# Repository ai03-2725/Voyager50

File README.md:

# Voyager50
A balance between function and size

[Supported layouts](http://www.keyboard-layout-editor.com/#/gists/caf09ce52668a0b0574eaae53debacd4)  

#### In light of recent claims that I am 100% liable for any of my open source PCBs, I am adding this disclaimer.
#### I provide these PCBs as a reference for designing keyboard PCBs. Using them within your projects will require a will to do research of one's own and to learn the workings of them, potentially fixing issues if they exist.
# I provide these PCBs without liability and without any guarantees regarding functionality, as expressed in the MIT license under which all of these PCBs are licensed.

### Features
* In-switch LED backlighting
* RGB underglow
* Decent amount of layout compatibility
* Over-current and static discharge protection
* Fully open-source

### The Voyager PCB Family
The Voyager PCBs offer fully featured PCBs fit for any keyboard, whether mass production or high-end.

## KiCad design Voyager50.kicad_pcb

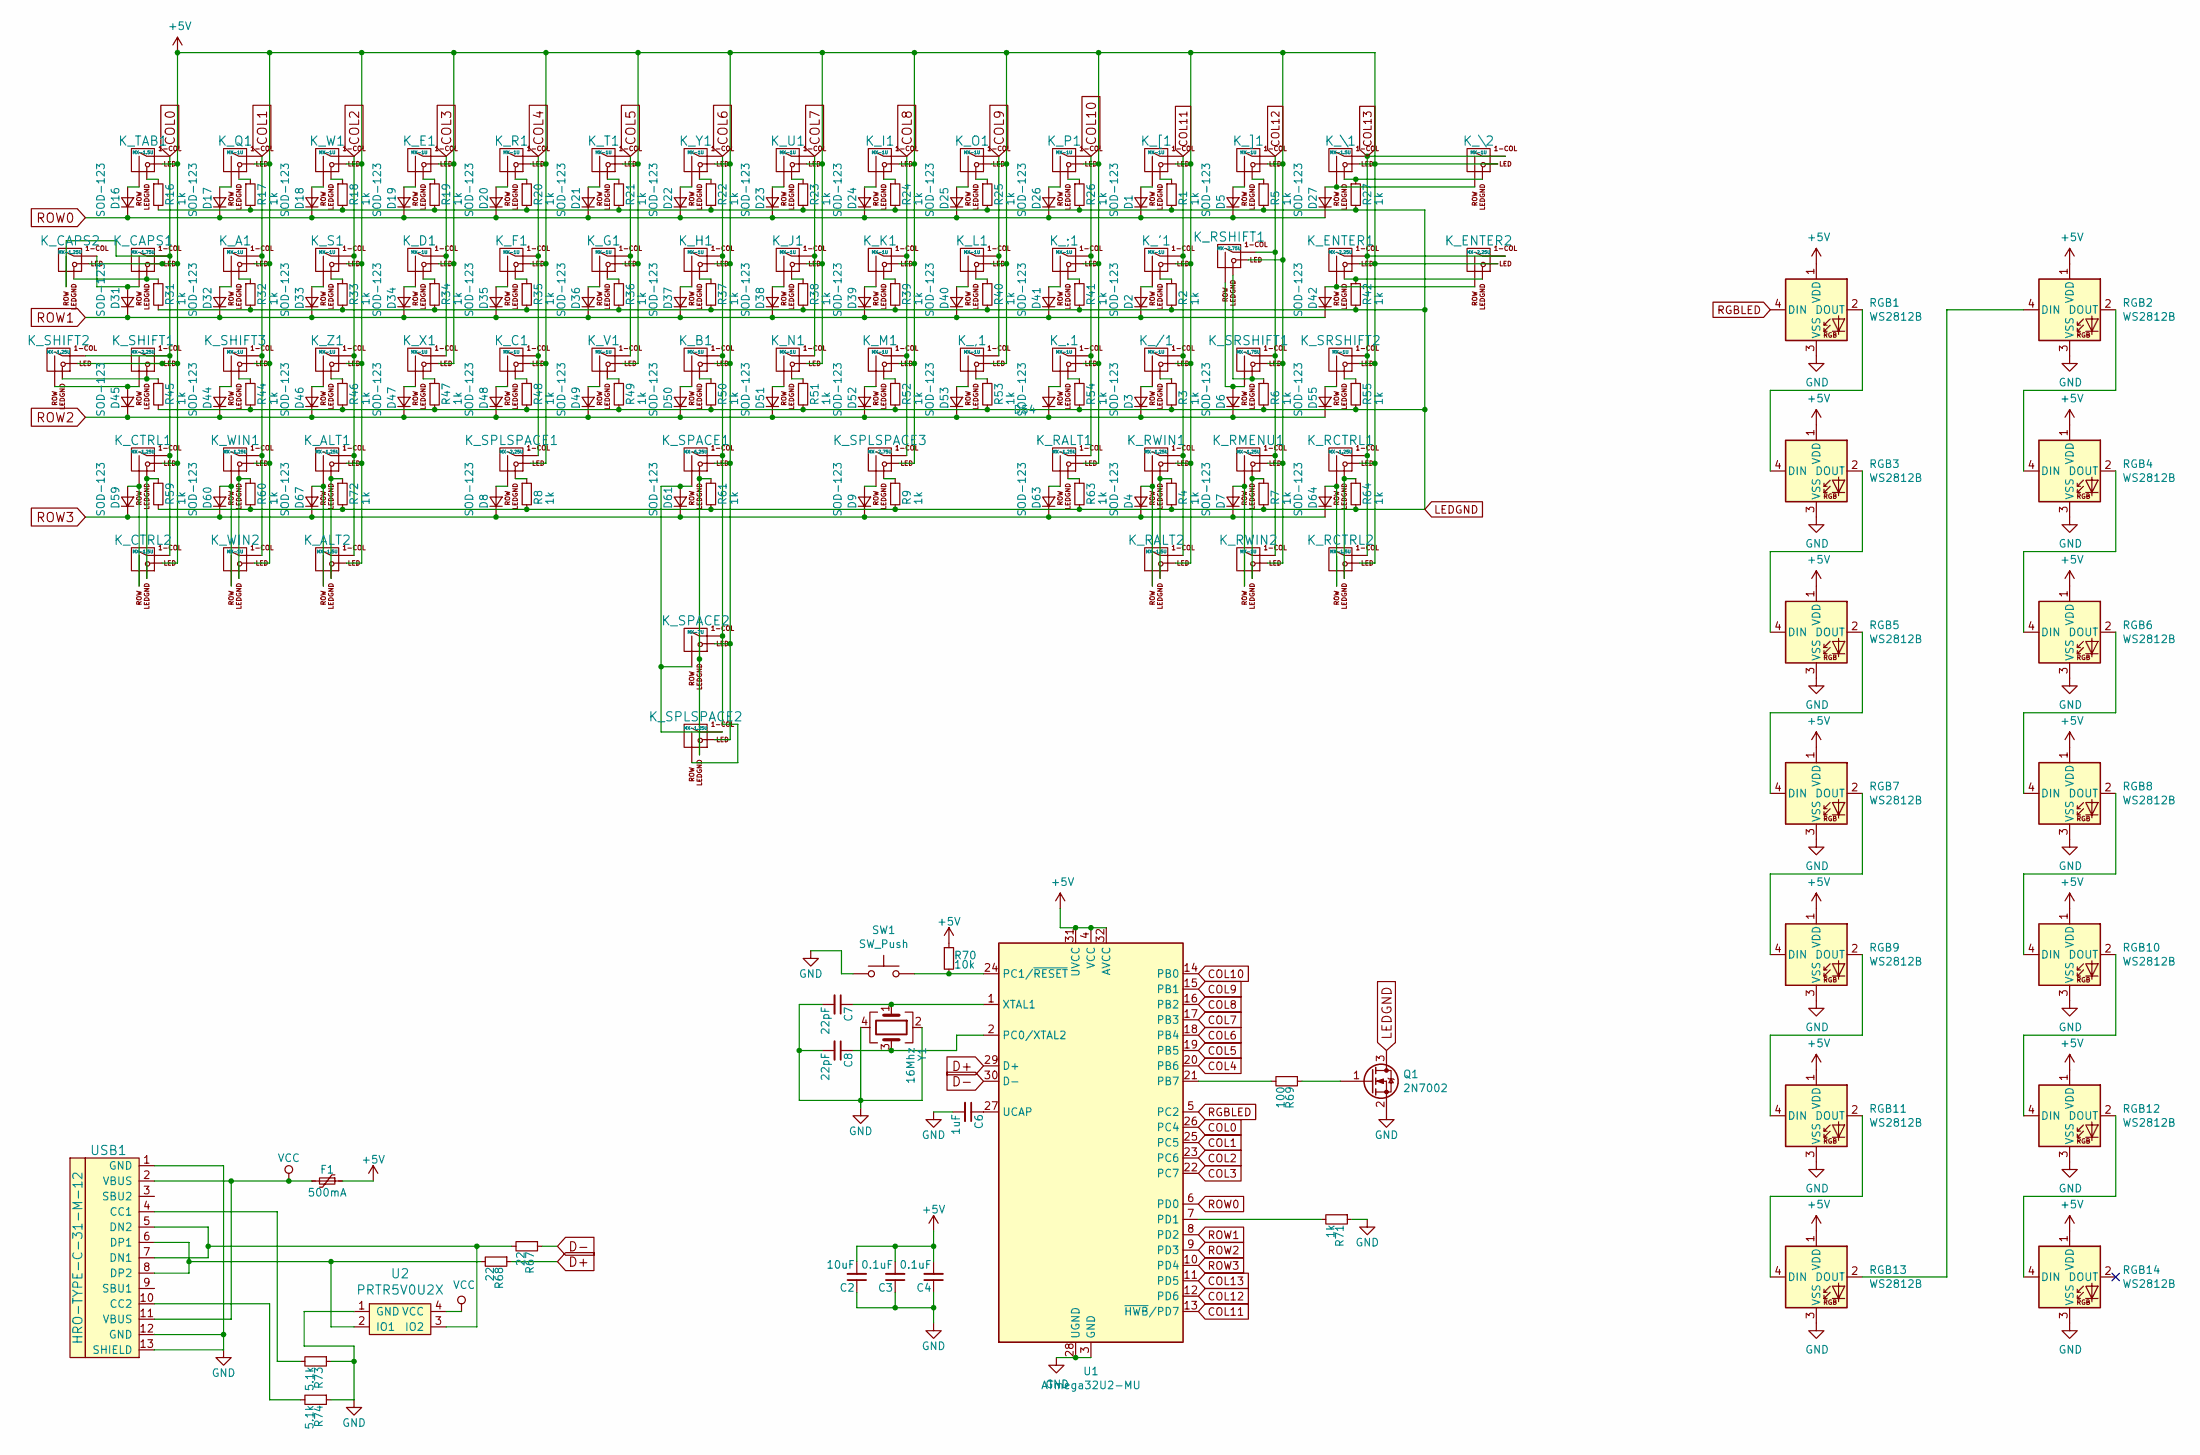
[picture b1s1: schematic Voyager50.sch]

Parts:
C2: 10uF; C_0603
C3, C4: 0.1uF; C_0603
C6: 1uF; C_0603
C7, C8: 22pF; C_0603
D1, D2, D3, D4, D5, D6, D7, D8, D9, D16, D17, D18, D19, D20, D21, D22, D23, D24, D25, D26, D27, D31, D32, D33, D34, D35, D36, D37, D38, D39, D40, D41, D42, D44, D45, D46, D47, D48, D49, D50, D51, D52, D53, D54, D55, D59, D60, D61, D63, D64, D67: SOD-123; D_SOD-123
F1: 500mA; Fuse_SMD1206_Reflow
K_'1: MX-1U
K_,1: MX-1U
K_.1: MX-1U
K_/1: MX-1U
K_;1: MX-1U
K_A1: MX-1U
K_ALT1: MX-1.25U
K_ALT2: MX-1.5U; MX-1.5U-FLIPPED
K_B1: MX-1U
K_C1: MX-1U
K_CAPS1: MX-1.75U
K_CAPS2: MX-1.25U; MX-1.25U-FLIPPED
K_CTRL1: MX-1.25U
K_CTRL2: MX-1.5U; MX-1.5U-FLIPPED
K_D1: MX-1U
K_E1: MX-1U
K_ENTER1: MX-2.25U
K_ENTER2: MX-2.25U; MX-ISO-ReversedStabilizers
K_F1: MX-1U
K_G1: MX-1U
K_H1: MX-1U
K_I1: MX-1U
K_J1: MX-1U
K_K1: MX-1U
K_L1: MX-1U
K_M1: MX-1U
K_N1: MX-1U
K_O1: MX-1U
K_P1: MX-1U
K_Q1: MX-1U
K_R1: MX-1U
K_RALT1: MX-1.25U
K_RALT2: MX-1.5U
K_RCTRL1: MX-1.25U; MX-1.25U-FLIPPED
K_RCTRL2: MX-1.5U
K_RMENU1: MX-1.25U; MX-1.25U-FLIPPED
K_RSHIFT1: MX-2.75U
K_RWIN1: MX-1.25U; MX-1.25U-FLIPPED
K_RWIN2: MX-1U
K_S1: MX-1U
K_SHIFT1: MX-2.25U
K_SHIFT2: MX-1.25U
K_SHIFT3: MX-1U
K_SPACE1: MX-6.25U; MX-6.25U-ReversedStabilizers
K_SPACE2: MX-7U; MX-7U-ReversedStabilizers
K_SPLSPACE1: MX-2.25U; MX-2.25U-ReversedStabilizers
K_SPLSPACE2: MX-1.25U; MX-1.25U-FLIPPED
K_SPLSPACE3: MX-2.75U; MX-2.75U-ReversedStabilizers
K_SRSHIFT1: MX-1.75U
K_SRSHIFT2: MX-1U
K_T1: MX-1U
K_TAB1: MX-1.5U
K_U1: MX-1U
K_V1: MX-1U
K_W1: MX-1U
K_WIN1: MX-1.25U
K_WIN2: MX-1U; MX-1U-FLIPPED
K_X1: MX-1U
K_Y1: MX-1U
K_Z1: MX-1U
K_[1: MX-1U
K_\1: MX-1.5U
K_\2: MX-1U
K_]1: MX-1U
Q1: 2N7002; SOT-23
R1, R2, R3, R4, R5, R6, R7, R8, R9, R16, R17, R18, R19, R20, R21, R22, R23, R24, R25, R26, R27, R31, R32, R33, R34, R35, R36, R37, R38, R39, R40, R41, R42, R44, R45, R46, R47, R48, R49, R50, R51, R52, R53, R54, R55, R59, R60, R61, R63, R64, R71, R72: 1k; R_0603
R67, R68: 22; R_0603
R69: 100; R_0603
R70: 10k; R_0603
R73, R74: 5.1k; R_0603
RGB1, RGB2, RGB3, RGB4, RGB5, RGB6, RGB7, RGB8, RGB9, RGB10, RGB11, RGB12, RGB13, RGB14: WS2812B; LED_WS2812B-PLCC4
SW1: SW_Push; SKQGADE010
U1: ATmega32U2-MU; QFN-32-1EP_5x5mm_Pitch0.5mm
U2: PRTR5V0U2X; SOT143B
USB1: HRO-TYPE-C-31-M-12; HRO-TYPE-C-31-M-12-Assembly
Y1: 16Mhz; Crystal_SMD_3225-4pin_3.2x2.5mm

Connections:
+5V: C2.2, C3.2, C4.2, F1.1, K_'1.3 (LED), K_,1.3 (LED), K_.1.3 (LED), K_/1.3 (LED), K_;1.3 (LED), K_A1.3 (LED), K_ALT1.3 (LED), K_ALT2.3 (LED), K_B1.3 (LED), K_C1.3 (LED), K_CAPS1.3 (LED), K_CAPS2.3 (LED), K_CTRL1.3 (LED), K_CTRL2.3 (LED), K_D1.3 (LED), K_E1.3 (LED), K_ENTER1.3 (LED), K_ENTER2.3 (LED), K_F1.3 (LED), K_G1.3 (LED), K_H1.3 (LED), K_I1.3 (LED), K_J1.3 (LED), K_K1.3 (LED), K_L1.3 (LED), K_M1.3 (LED), K_N1.3 (LED), K_O1.3 (LED), K_P1.3 (LED), K_Q1.3 (LED), K_R1.3 (LED), K_RALT1.3 (LED), K_RALT2.3 (LED), K_RCTRL1.3 (LED), K_RCTRL2.3 (LED), K_RMENU1.3 (LED), K_RSHIFT1.3 (LED), K_RWIN1.3 (LED), K_RWIN2.3 (LED), K_S1.3 (LED), K_SHIFT1.3 (LED), K_SHIFT2.3 (LED), K_SHIFT3.3 (LED), K_SPACE1.3 (LED), K_SPACE2.3 (LED), K_SPLSPACE1.3 (LED), K_SPLSPACE2.3 (LED), K_SPLSPACE3.3 (LED), K_SRSHIFT1.3 (LED), K_SRSHIFT2.3 (LED), K_T1.3 (LED), K_TAB1.3 (LED), K_U1.3 (LED), K_V1.3 (LED), K_W1.3 (LED), K_WIN1.3 (LED), K_WIN2.3 (LED), K_X1.3 (LED), K_Y1.3 (LED), K_Z1.3 (LED), K_[1.3 (LED), K_\1.3 (LED), K_\2.3 (LED), K_]1.3 (LED), R70.1, RGB1.1 (VDD), RGB2.1 (VDD), RGB3.1 (VDD), RGB4.1 (VDD), RGB5.1 (VDD), RGB6.1 (VDD), RGB7.1 (VDD), RGB8.1 (VDD), RGB9.1 (VDD), RGB10.1 (VDD), RGB11.1 (VDD), RGB12.1 (VDD), RGB13.1 (VDD), RGB14.1 (VDD), U1.4 (VCC), U1.31 (UVCC), U1.32 (AVCC)
COL0: K_CAPS1.1 (COL), K_CAPS2.2 (ROW), K_CTRL1.1 (COL), K_CTRL2.1 (COL), K_SHIFT1.1 (COL), K_SHIFT2.1 (COL), K_TAB1.1 (COL), U1.26 (PC4)
COL1: K_A1.1 (COL), K_Q1.1 (COL), K_SHIFT3.1 (COL), K_WIN1.1 (COL), K_WIN2.1 (COL), U1.25 (PC5)
COL2: K_ALT1.1 (COL), K_ALT2.1 (COL), K_S1.1 (COL), K_W1.1 (COL), K_Z1.1 (COL), U1.23 (PC6)
COL3: K_D1.1 (COL), K_E1.1 (COL), K_X1.1 (COL), U1.22 (PC7)
COL4: K_C1.1 (COL), K_F1.1 (COL), K_R1.1 (COL), K_SPLSPACE1.1 (COL), U1.20 (PB6)
COL5: K_G1.1 (COL), K_T1.1 (COL), K_V1.1 (COL), U1.19 (PB5)
COL6: K_B1.1 (COL), K_H1.1 (COL), K_SPACE1.1 (COL), K_SPACE2.1 (COL), K_SPLSPACE2.2 (ROW), K_Y1.1 (COL), U1.18 (PB4)
COL7: K_J1.1 (COL), K_N1.1 (COL), K_U1.1 (COL), U1.17 (PB3)
COL8: K_I1.1 (COL), K_K1.1 (COL), K_M1.1 (COL), K_SPLSPACE3.1 (COL), U1.16 (PB2)
COL9: K_,1.1 (COL), K_L1.1 (COL), K_O1.1 (COL), U1.15 (PB1)
COL10: K_.1.1 (COL), K_;1.1 (COL), K_P1.1 (COL), K_RALT1.1 (COL), U1.14 (PB0)
COL11: K_'1.1 (COL), K_/1.1 (COL), K_RALT2.1 (COL), K_RWIN1.1 (COL), K_[1.1 (COL), U1.13 (~HWB~/PD7)
COL12: K_RMENU1.1 (COL), K_RSHIFT1.1 (COL), K_RWIN2.1 (COL), K_SRSHIFT1.1 (COL), K_]1.1 (COL), U1.12 (PD6)
COL13: K_ENTER1.1 (COL), K_ENTER2.1 (COL), K_RCTRL1.1 (COL), K_RCTRL2.1 (COL), K_SRSHIFT2.1 (COL), K_\1.1 (COL), K_\2.1 (COL), U1.11 (PD5)
D+: R68.1, U1.29 (D+)
D-: R67.1, U1.30 (D-)
GND: C2.1, C3.1, C4.1, C6.2, C7.2, C8.2, Q1.2 (S), R71.1, R73.1, R74.1, RGB1.3 (VSS), RGB2.3 (VSS), RGB3.3 (VSS), RGB4.3 (VSS), RGB5.3 (VSS), RGB6.3 (VSS), RGB7.3 (VSS), RGB8.3 (VSS), RGB9.3 (VSS), RGB10.3 (VSS), RGB11.3 (VSS), RGB12.3 (VSS), RGB13.3 (VSS), RGB14.3 (VSS), SW1.1, U1.3 (GND), U1.28 (UGND), U1.33 (GND), U2.1 (GND), USB1.1 (GND), USB1.12 (GND), USB1.13 (SHIELD), Y1.2, Y1.4
LEDGND: Q1.3 (D), R1.2, R2.2, R3.2, R4.2, R5.2, R6.2, R7.2, R8.2, R9.2, R16.2, R17.2, R18.2, R19.2, R20.2, R21.2, R22.2, R23.2, R24.2, R25.2, R26.2, R27.2, R31.2, R32.2, R33.2, R34.2, R35.2, R36.2, R37.2, R38.2, R39.2, R40.2, R41.2, R42.2, R44.2, R45.2, R46.2, R47.2, R48.2, R49.2, R50.2, R51.2, R52.2, R53.2, R54.2, R55.2, R59.2, R60.2, R61.2, R63.2, R64.2, R72.2
unnamed: C6.1, U1.27 (UCAP)
unnamed: C7.1, U1.1 (XTAL1), Y1.1
unnamed: C8.1, U1.2 (PC0/XTAL2), Y1.3
unnamed: D1.2 (A), K_[1.2 (ROW)
unnamed: D2.2 (A), K_'1.2 (ROW)
unnamed: D3.2 (A), K_/1.2 (ROW)
unnamed: D4.2 (A), K_RALT2.2 (ROW), K_RWIN1.2 (ROW)
unnamed: D5.2 (A), K_]1.2 (ROW)
unnamed: D6.2 (A), K_RSHIFT1.2 (ROW), K_SRSHIFT1.2 (ROW)
unnamed: D7.2 (A), K_RMENU1.2 (ROW), K_RWIN2.2 (ROW)
unnamed: D8.2 (A), K_SPLSPACE1.2 (ROW)
unnamed: D9.2 (A), K_SPLSPACE3.2 (ROW)
unnamed: D16.2 (A), K_TAB1.2 (ROW)
unnamed: D17.2 (A), K_Q1.2 (ROW)
unnamed: D18.2 (A), K_W1.2 (ROW)
unnamed: D19.2 (A), K_E1.2 (ROW)
unnamed: D20.2 (A), K_R1.2 (ROW)
unnamed: D21.2 (A), K_T1.2 (ROW)
unnamed: D22.2 (A), K_Y1.2 (ROW)
unnamed: D23.2 (A), K_U1.2 (ROW)
unnamed: D24.2 (A), K_I1.2 (ROW)
unnamed: D25.2 (A), K_O1.2 (ROW)
unnamed: D26.2 (A), K_P1.2 (ROW)
unnamed: D27.2 (A), K_\1.2 (ROW), K_\2.2 (ROW)
unnamed: D31.2 (A), K_CAPS1.2 (ROW), K_CAPS2.1 (COL)
unnamed: D32.2 (A), K_A1.2 (ROW)
unnamed: D33.2 (A), K_S1.2 (ROW)
unnamed: D34.2 (A), K_D1.2 (ROW)
unnamed: D35.2 (A), K_F1.2 (ROW)
unnamed: D36.2 (A), K_G1.2 (ROW)
unnamed: D37.2 (A), K_H1.2 (ROW)
unnamed: D38.2 (A), K_J1.2 (ROW)
unnamed: D39.2 (A), K_K1.2 (ROW)
unnamed: D40.2 (A), K_L1.2 (ROW)
unnamed: D41.2 (A), K_;1.2 (ROW)
unnamed: D42.2 (A), K_ENTER1.2 (ROW), K_ENTER2.2 (ROW)
unnamed: D44.2 (A), K_SHIFT3.2 (ROW)
unnamed: D45.2 (A), K_SHIFT1.2 (ROW), K_SHIFT2.2 (ROW)
unnamed: D46.2 (A), K_Z1.2 (ROW)
unnamed: D47.2 (A), K_X1.2 (ROW)
unnamed: D48.2 (A), K_C1.2 (ROW)
unnamed: D49.2 (A), K_V1.2 (ROW)
unnamed: D50.2 (A), K_B1.2 (ROW)
unnamed: D51.2 (A), K_N1.2 (ROW)
unnamed: D52.2 (A), K_M1.2 (ROW)
unnamed: D53.2 (A), K_,1.2 (ROW)
unnamed: D54.2 (A), K_.1.2 (ROW)
unnamed: D55.2 (A), K_SRSHIFT2.2 (ROW)
unnamed: D59.2 (A), K_CTRL1.2 (ROW), K_CTRL2.2 (ROW)
unnamed: D60.2 (A), K_WIN1.2 (ROW), K_WIN2.2 (ROW)
unnamed: D61.2 (A), K_SPACE1.2 (ROW), K_SPACE2.2 (ROW), K_SPLSPACE2.1 (COL)
unnamed: D63.2 (A), K_RALT1.2 (ROW)
unnamed: D64.2 (A), K_RCTRL1.2 (ROW), K_RCTRL2.2 (ROW)
unnamed: D67.2 (A), K_ALT1.2 (ROW), K_ALT2.2 (ROW)
unnamed: K_'1.4 (LEDGND), R2.1
unnamed: K_,1.4 (LEDGND), R53.1
unnamed: K_.1.4 (LEDGND), R54.1
unnamed: K_/1.4 (LEDGND), R3.1
unnamed: K_;1.4 (LEDGND), R41.1
unnamed: K_A1.4 (LEDGND), R32.1
unnamed: K_ALT1.4 (LEDGND), K_ALT2.4 (LEDGND), R72.1
unnamed: K_B1.4 (LEDGND), R50.1
unnamed: K_C1.4 (LEDGND), R48.1
unnamed: K_CAPS1.4 (LEDGND), K_CAPS2.4 (LEDGND), R31.1
unnamed: K_CTRL1.4 (LEDGND), K_CTRL2.4 (LEDGND), R59.1
unnamed: K_D1.4 (LEDGND), R34.1
unnamed: K_E1.4 (LEDGND), R19.1
unnamed: K_ENTER1.4 (LEDGND), K_ENTER2.4 (LEDGND), R42.1
unnamed: K_F1.4 (LEDGND), R35.1
unnamed: K_G1.4 (LEDGND), R36.1
unnamed: K_H1.4 (LEDGND), R37.1
unnamed: K_I1.4 (LEDGND), R24.1
unnamed: K_J1.4 (LEDGND), R38.1
unnamed: K_K1.4 (LEDGND), R39.1
unnamed: K_L1.4 (LEDGND), R40.1
unnamed: K_M1.4 (LEDGND), R52.1
unnamed: K_N1.4 (LEDGND), R51.1
unnamed: K_O1.4 (LEDGND), R25.1
unnamed: K_P1.4 (LEDGND), R26.1
unnamed: K_Q1.4 (LEDGND), R17.1
unnamed: K_R1.4 (LEDGND), R20.1
unnamed: K_RALT1.4 (LEDGND), R63.1
unnamed: K_RALT2.4 (LEDGND), K_RWIN1.4 (LEDGND), R4.1
unnamed: K_RCTRL1.4 (LEDGND), K_RCTRL2.4 (LEDGND), R64.1
unnamed: K_RMENU1.4 (LEDGND), K_RWIN2.4 (LEDGND), R7.1
unnamed: K_RSHIFT1.4 (LEDGND), K_SRSHIFT1.4 (LEDGND), R6.1
unnamed: K_S1.4 (LEDGND), R33.1
unnamed: K_SHIFT1.4 (LEDGND), K_SHIFT2.4 (LEDGND), R45.1
unnamed: K_SHIFT3.4 (LEDGND), R44.1
unnamed: K_SPACE1.4 (LEDGND), K_SPACE2.4 (LEDGND), K_SPLSPACE2.4 (LEDGND), R61.1
unnamed: K_SPLSPACE1.4 (LEDGND), R8.1
unnamed: K_SPLSPACE3.4 (LEDGND), R9.1
unnamed: K_SRSHIFT2.4 (LEDGND), R55.1
unnamed: K_T1.4 (LEDGND), R21.1
unnamed: K_TAB1.4 (LEDGND), R16.1
unnamed: K_U1.4 (LEDGND), R23.1
unnamed: K_V1.4 (LEDGND), R49.1
unnamed: K_W1.4 (LEDGND), R18.1
unnamed: K_WIN1.4 (LEDGND), K_WIN2.4 (LEDGND), R60.1
unnamed: K_X1.4 (LEDGND), R47.1
unnamed: K_Y1.4 (LEDGND), R22.1
unnamed: K_Z1.4 (LEDGND), R46.1
unnamed: K_[1.4 (LEDGND), R1.1
unnamed: K_\1.4 (LEDGND), K_\2.4 (LEDGND), R27.1
unnamed: K_]1.4 (LEDGND), R5.1
unnamed: Q1.1 (G), R69.1
unnamed: R67.2, U2.3 (IO2), USB1.5 (DN2), USB1.7 (DN1)
unnamed: R68.2, U2.2 (IO1), USB1.6 (DP1), USB1.8 (DP2)
unnamed: R69.2, U1.21 (PB7)
unnamed: R70.2, SW1.2, U1.24 (PC1/~RESET)
unnamed: R71.2, U1.7 (PD1)
unnamed: R73.2, USB1.4 (CC1)
unnamed: R74.2, USB1.10 (CC2)
unnamed: RGB1.2 (DOUT), RGB3.4 (DIN)
unnamed: RGB2.2 (DOUT), RGB4.4 (DIN)
unnamed: RGB3.2 (DOUT), RGB5.4 (DIN)
unnamed: RGB4.2 (DOUT), RGB6.4 (DIN)
unnamed: RGB5.2 (DOUT), RGB7.4 (DIN)
unnamed: RGB6.2 (DOUT), RGB8.4 (DIN)
unnamed: RGB7.2 (DOUT), RGB9.4 (DIN)
unnamed: RGB10.2 (DOUT), RGB12.4 (DIN)
unnamed: RGB8.2 (DOUT), RGB10.4 (DIN)
unnamed: RGB11.2 (DOUT), RGB13.4 (DIN)
unnamed: RGB9.2 (DOUT), RGB11.4 (DIN)
unnamed: RGB12.2 (DOUT), RGB14.4 (DIN)
unnamed: RGB2.4 (DIN), RGB13.2 (DOUT)
RGBLED: RGB1.4 (DIN), U1.5 (PC2)
ROW0: D1.1 (K), D5.1 (K), D16.1 (K), D17.1 (K), D18.1 (K), D19.1 (K), D20.1 (K), D21.1 (K), D22.1 (K), D23.1 (K), D24.1 (K), D25.1 (K), D26.1 (K), D27.1 (K), U1.6 (PD0)
ROW1: D2.1 (K), D31.1 (K), D32.1 (K), D33.1 (K), D34.1 (K), D35.1 (K), D36.1 (K), D37.1 (K), D38.1 (K), D39.1 (K), D40.1 (K), D41.1 (K), D42.1 (K), U1.8 (PD2)
ROW2: D3.1 (K), D6.1 (K), D44.1 (K), D45.1 (K), D46.1 (K), D47.1 (K), D48.1 (K), D49.1 (K), D50.1 (K), D51.1 (K), D52.1 (K), D53.1 (K), D54.1 (K), D55.1 (K), U1.9 (PD3)
ROW3: D4.1 (K), D7.1 (K), D8.1 (K), D9.1 (K), D59.1 (K), D60.1 (K), D61.1 (K), D63.1 (K), D64.1 (K), D67.1 (K), U1.10 (PD4)
VCC: F1.2, U2.4 (VCC), USB1.2 (VBUS), USB1.11 (VBUS)

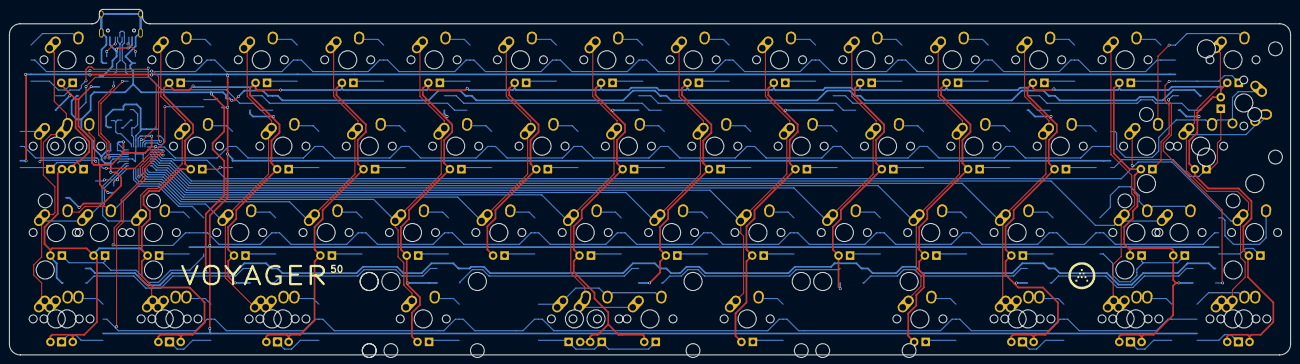
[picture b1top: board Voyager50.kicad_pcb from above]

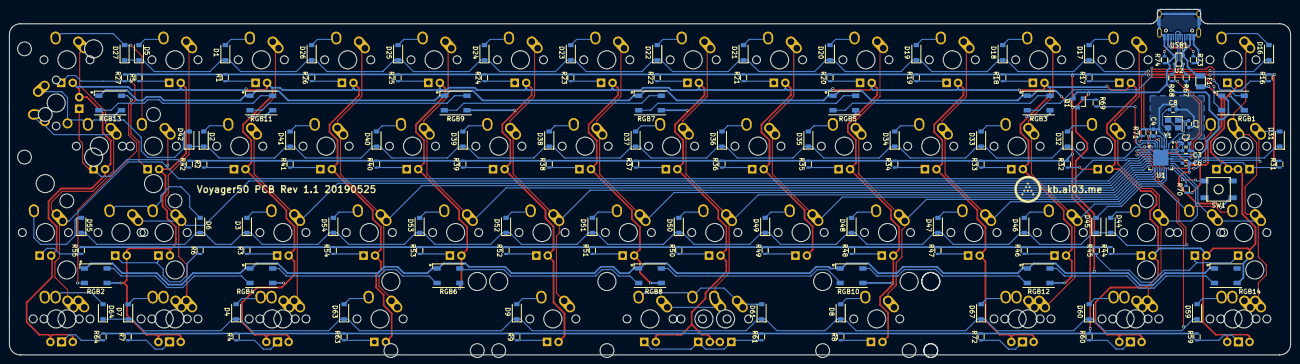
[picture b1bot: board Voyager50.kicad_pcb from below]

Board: 2 copper layers, 282.6 x 76.2 mm, 200 parts (136 on the bottom side), 151 nets.

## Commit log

2019-05-24 Populate base files
2019-05-25 Finish routing
2019-05-25 Update render, add gerbers
2019-05-25 Add split space
2019-05-26 Update fp-info-cache
